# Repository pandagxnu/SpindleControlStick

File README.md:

SpindleControlStick
===================

Spindle Controller for Cyclone PCB Factory.

This is a simple Spindle Controller (Relay On/Off). Compatible with a Pololu StepStick Socket.

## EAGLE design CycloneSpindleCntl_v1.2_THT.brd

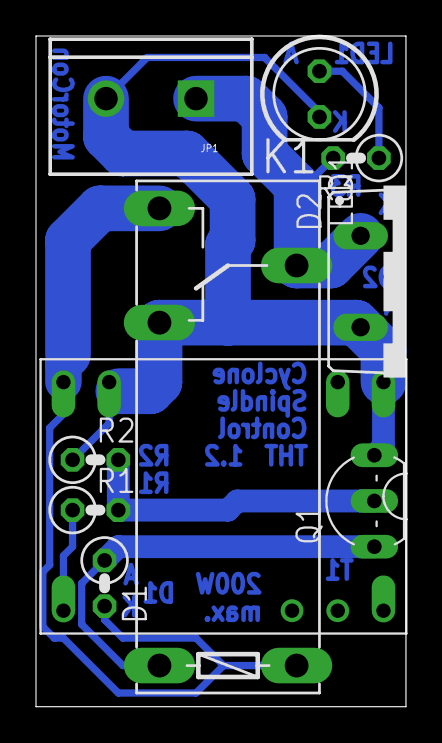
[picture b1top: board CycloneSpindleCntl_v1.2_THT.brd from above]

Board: 2 copper layers, 20.6 x 37.3 mm, 10 parts (0 on the bottom side), 7 nets.

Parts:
D1: 1N4148; 0207/2V
D2: MBR1645; TO220ACS
JP1: Spindle; SCREWTERMINAL-5MM-2
K1: G6RW
LED1: GREEN; LED5MM
Q1: BC548; TO92-EBC
R1: 2k; 0207/2V
R2: 100k; 0207/2V
R3: 22R; 0207/2V
U$1: SPINDLEDRIVERSTICK; DIL16_MOD

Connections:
+12V: D1.2, K1.1, K1.S, U$1.8
GND: D2.A, JP1.2, K1.O, LED1.K, Q1.E, R2.1, U$1.1, U$1.7
unnamed: LED1.A, R3.1
unnamed: Q1.B, R1.2, R2.2
unnamed: D1.1, K1.2, Q1.C
unnamed: D2.C, JP1.1, K1.P, R3.2
unnamed: R1.1, U$1.9

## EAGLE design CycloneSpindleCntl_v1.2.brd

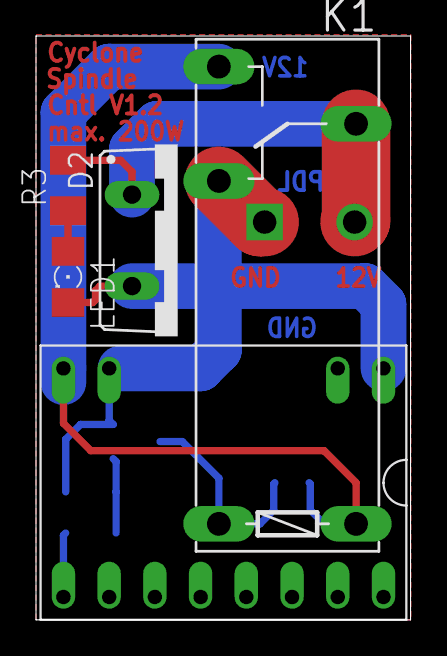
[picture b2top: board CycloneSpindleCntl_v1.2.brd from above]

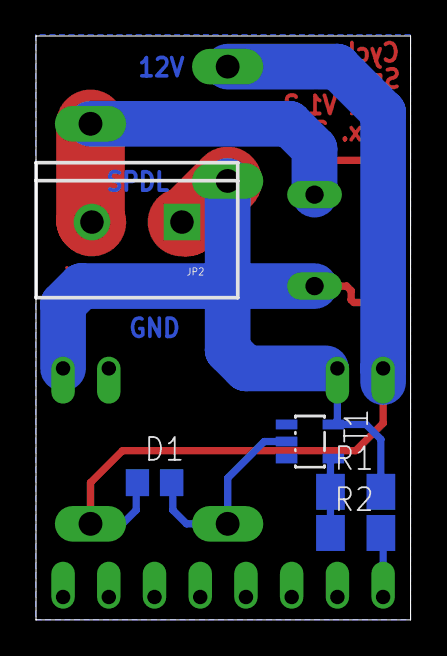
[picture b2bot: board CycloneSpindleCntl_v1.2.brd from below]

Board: 2 copper layers, 20.8 x 32.4 mm, 10 parts (5 on the bottom side), 7 nets.

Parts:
D1: 1N4148; R0805
D2: MBR1645; TO220ACS
JP2: Spindle; SCREWTERMINAL-5MM-2
K1: G6RW
LED1: 1206
R1: 100k; M1206
R2, R3: 22R; M1206
T1: BSS138; SOT23-5L
U$1: SPINDLEDRIVERSTICK; DIL16_MOD

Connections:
+12V: D1.K, K1.1, K1.S, U$1.8
GND: D2.A, JP2.1, K1.O, LED1.C, R1.2, T1.5, U$1.1, U$1.7
unnamed: LED1.A, R3.1
unnamed: D1.A, K1.2, T1.2
unnamed: R1.1, R2.1, T1.4
unnamed: D2.C, JP2.2, K1.P, R3.2
unnamed: R2.2, U$1.9

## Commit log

2013-08-28 Version 1.2
2013-08-31 THT Version

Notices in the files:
parts and their libraries:
SparkFun-Connectors: Licensing: CC v3.0 Share-Alike You are welcome to use this library for commercial purposes.
